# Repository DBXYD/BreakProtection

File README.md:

# 3A_BREAK

## Components
* MOSFET de puissance, Canal N, 100 V, 31 A, 0.031 ohm, TO-263 (D2PAK), Montage en surface :  
https://fr.farnell.com/nexperia/buk9637-100e-118/mosfet-n-ch-100v-31a-d2pak/dp/2254193

* Régulateur à découpage Buck (Step Down), Fixe, Entrée 7.5V à 76V, Sortie 5V 500mA 125 kHz NSOIC-8 :  
https://fr.farnell.com/maxim-integrated-products/max5033busa/convertisseur-dc-dc-buck-125khz/dp/2513947

* Redresseur Schottky, 100 V, 2 A, Une, DO-220AA, 2 Broche(s), 800 mV :  
https://fr.farnell.com/vishay/ss2ph10-m3-84a/diode-rectifier-schottky-2a-100v/dp/1812489

* WE-PDA SMT Shielded Power Inductor EXTENDED - 784771221 - 220uH 0.99A :  
https://www.we-online.com/catalog/en/WE-PDA?sq=784771221#784771221

* Carte de développement, MCU Nucleo-G431KB, STM32G431KBT6U, Arduino Nano V3 :   
https://fr.farnell.com/stmicroelectronics/nucleo-g431kb/carte-de-dev-32-bits-arm-cortex/dp/3132398

* Bornier fil-à-carte, 5.08 mm, 2 Voies, 26 AWG, 12 AWG, 4 mm², Par vis :  
https://fr.farnell.com/multicomp/mc000034/bornier-ci-noir-5-08mm-vis-02/dp/2008004

* CI Driver de MOSFET, Low Side, Alimentation 4.5V à 16V, 2A Out, 35ns Retard, SOIC-8 :  
https://fr.farnell.com/microchip/tc1412neoa/driver-mosfet-2a-non-inv-8soic/dp/1834898

* Redresseur Schottky, 60 V, 15 A, Une, TO-263AB, 3 Broche(s), 620 mV :  
https://fr.farnell.com/vishay/vs-15tq060s-m3/diode-schottky-simple-60v-to263ab/dp/2909608

* Codeur rotatif, Mécanique, Incrémental, 15 PPR, 30 crans, Verticale, Avec commutateur push :  
https://fr.farnell.com/wurth-elektronik/482016514001/codeur-rotatif-mecanique-incremental/dp/3806131?ost=3806131

* Afficheur LCD, Grove, LCD RGB 16X2 rétroéclairage, Interface I2C :  
https://fr.farnell.com/seeed-studio/104030001/grove-cran-lcd-rvb-r-tro-clair/dp/3932101

## Tools

* Calcul isolement :  
https://www.smps.us/pcbtracespacing.html

## Export Gerber 

CAM Processor
CAMOutputs

### LPKF
* Switch on LPKF
* Open LPKF CircuitPro PM 2.7 software
* Wait few minutes
* Choose Template DoubleSided_Galvanic_THP
* Check Machining -> Connect... (if not) -> S62
* Calibration Key is incorrect -> ok
* Import Data from a non-native format 
* -> Import all gerbers and drillfiles
* Generate isolation and contour -> 35um
* Process -> 4/4

### Photo-ploter
* Gerb2BMP : 
* Import Master Gerber
* Copper_Top // Copper_botton
* Export Gerber to bitmap file (2032 dpi)

* Filmstar : Generate and run on photoploter
* CUIVRE : NEGATIVE !!!
*

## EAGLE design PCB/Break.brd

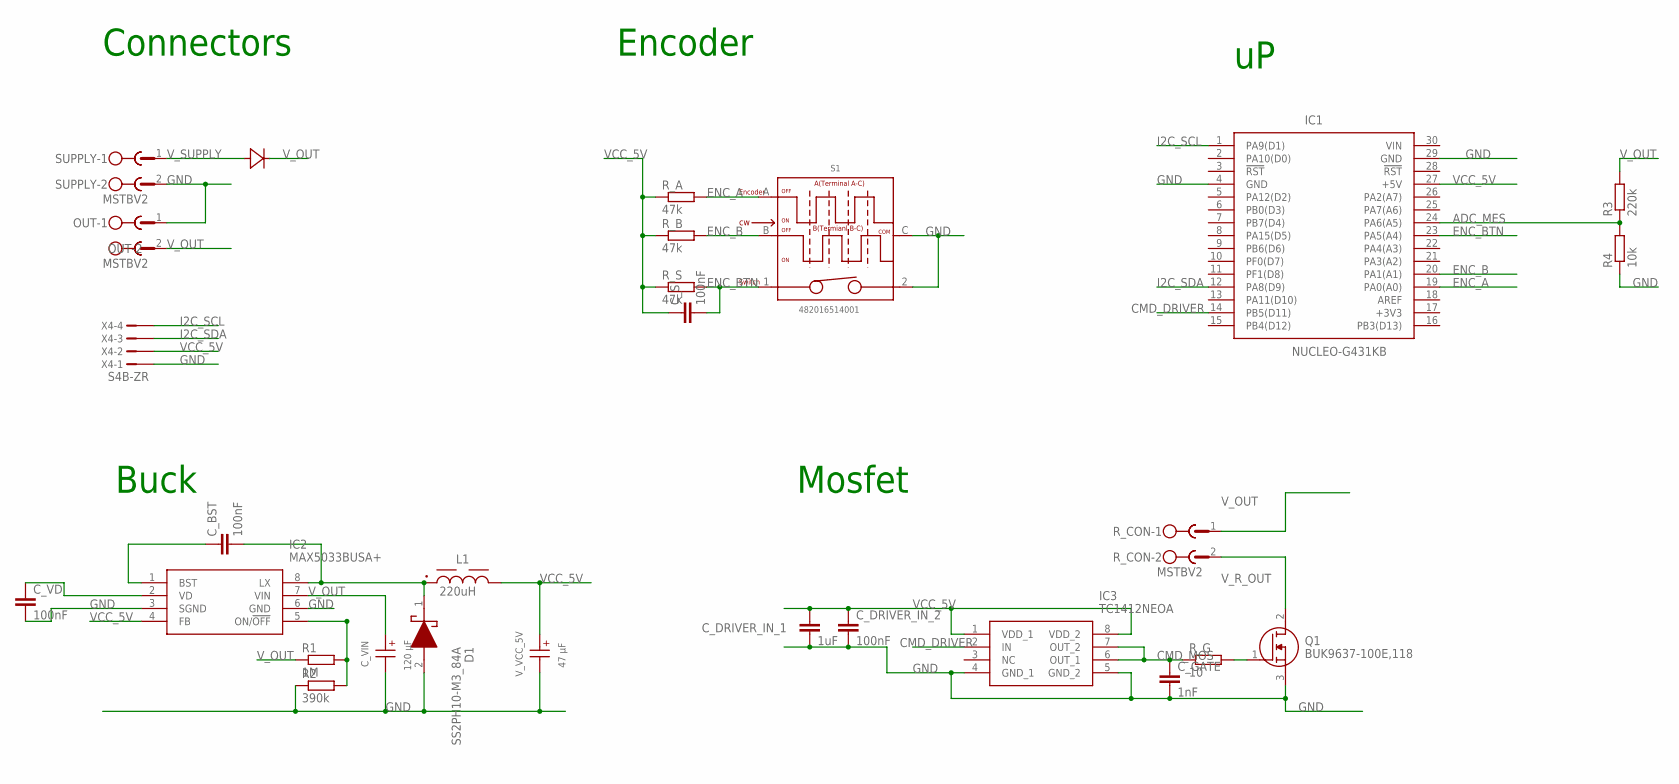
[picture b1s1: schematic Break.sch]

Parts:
C_BST: 100nF; C0603
C_DRIVER_IN_1: 1uF; C0603
C_DRIVER_IN_2: 100nF; C0603
C_GATE: 1nF; C0603
C_S: 100nF; C0603
C_VD: 100nF; C0603
C_VIN: 120 µF; WCAP-ATG8_18X41X7.5(DXL)
D1: SS2PH10-M3_84A; DO-220AA
IC1: NUCLEO-G431KB; DIPS1524W66P254L5029H1500Q30N
IC2: MAX5033BUSA+; SOIC127P600X175-8N
IC3: TC1412NEOA; SOIC127P600X175-8N
L1: 220uH; WE-PDA_1260
OUT: MSTBV2
Q1: BUK9637-100E,118; PSMN4R480BS118
R1: 1M; R0603
R2: 390k; R0603
R3: 220k; R0603
R4: 10k; R0603
R_A: 47k; R0603
R_B: 47k; R0603
R_CON: MSTBV2
R_G: 10; R1206
R_S: 47k; R0603
S1: 482016514001; WS-ENTV_4820XX514001
SUPPLY: MSTBV2
U$1: VS-15TG060S-M3; SMD-220
V_VCC_5V: 47 µF; WCAP-ASLL_6.3X5.5(DXL)
X4: S4B-ZR

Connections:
ADC_MES: IC1.24 (PA6(A5)), R3.1, R4.2
CMD_DRIVER: IC1.14 (PB5(D11)), IC3.2 (IN)
CMD_MOS: C_GATE.1, IC3.6 (OUT_1), IC3.7 (OUT_2), R_G.1
ENC_A: IC1.19 (PA0(A0)), R_A.2, S1.A
ENC_B: IC1.20 (PA1(A1)), R_B.2, S1.B
ENC_BTN: C_S.2, IC1.23 (PA5(A4)), R_S.2, S1.1
GND: C_DRIVER_IN_1.2, C_DRIVER_IN_2.2, C_GATE.2, C_VD.2, C_VIN.2 (-), D1.2 (A), IC1.4 (GND), IC1.29 (GND), IC2.3 (SGND), IC2.6 (GND), IC3.4 (GND_1), IC3.5 (GND_2), OUT.1, Q1.3 (S), R2.1, R4.1, S1.2, S1.C (COM), SUPPLY.2, V_VCC_5V.2 (-), X4.1
I2C_SCL: IC1.1 (PA9(D1)), X4.4
I2C_SDA: IC1.12 (PA8(D9)), X4.3
unnamed: Q1.1 (G), R_G.2
unnamed: C_BST.2, D1.1 (K), IC2.8 (LX), L1.1
unnamed: C_VD.1, IC2.2 (VD)
unnamed: C_BST.1, IC2.1 (BST)
unnamed: IC2.5 (ON/!OFF), R1.2, R2.2
VCC_5V: C_DRIVER_IN_1.1, C_DRIVER_IN_2.1, C_S.1, IC1.27 (+5V), IC2.4 (FB), IC3.1 (VDD_1), IC3.8 (VDD_2), L1.2, R_A.1, R_B.1, R_S.1, V_VCC_5V.1 (+), X4.2
V_OUT: C_VIN.1 (+), IC2.7 (VIN), OUT.2, R1.1, R3.2, R_CON.1, U$1.P$4 (C)
V_R_OUT: Q1.2 (D), R_CON.2
V_SUPPLY: SUPPLY.1, U$1.P$3 (A)

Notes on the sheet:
Connectors
Buck
Mosfet
Encoder

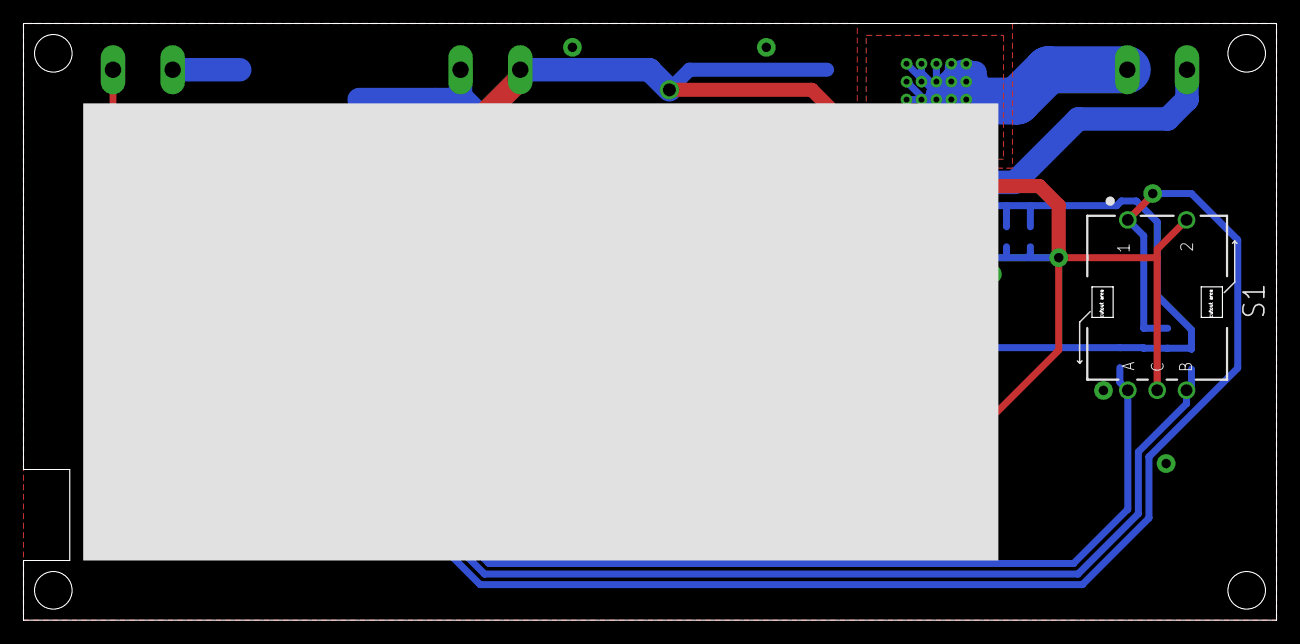
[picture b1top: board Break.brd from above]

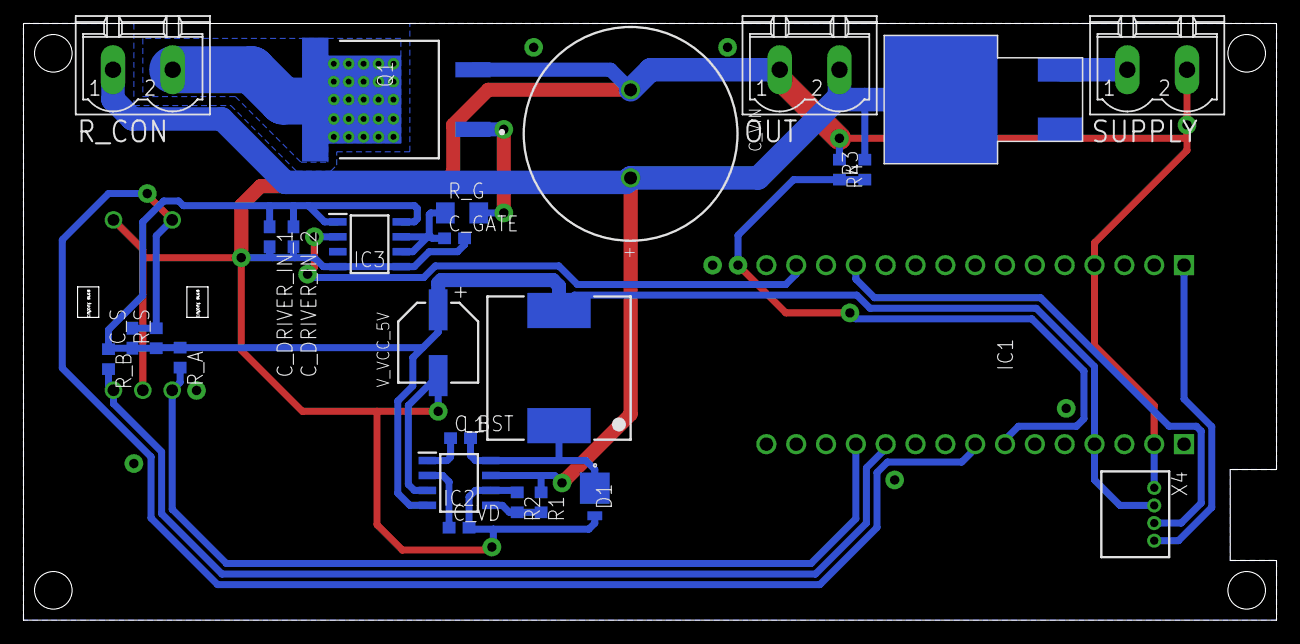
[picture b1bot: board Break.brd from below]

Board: 2 copper layers, 106.6 x 50.7 mm, 28 parts (27 on the bottom side), 18 nets.

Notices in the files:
parts and their libraries:
Eagle_WCAP-ATG8: Copyright: Würth Elektronik
